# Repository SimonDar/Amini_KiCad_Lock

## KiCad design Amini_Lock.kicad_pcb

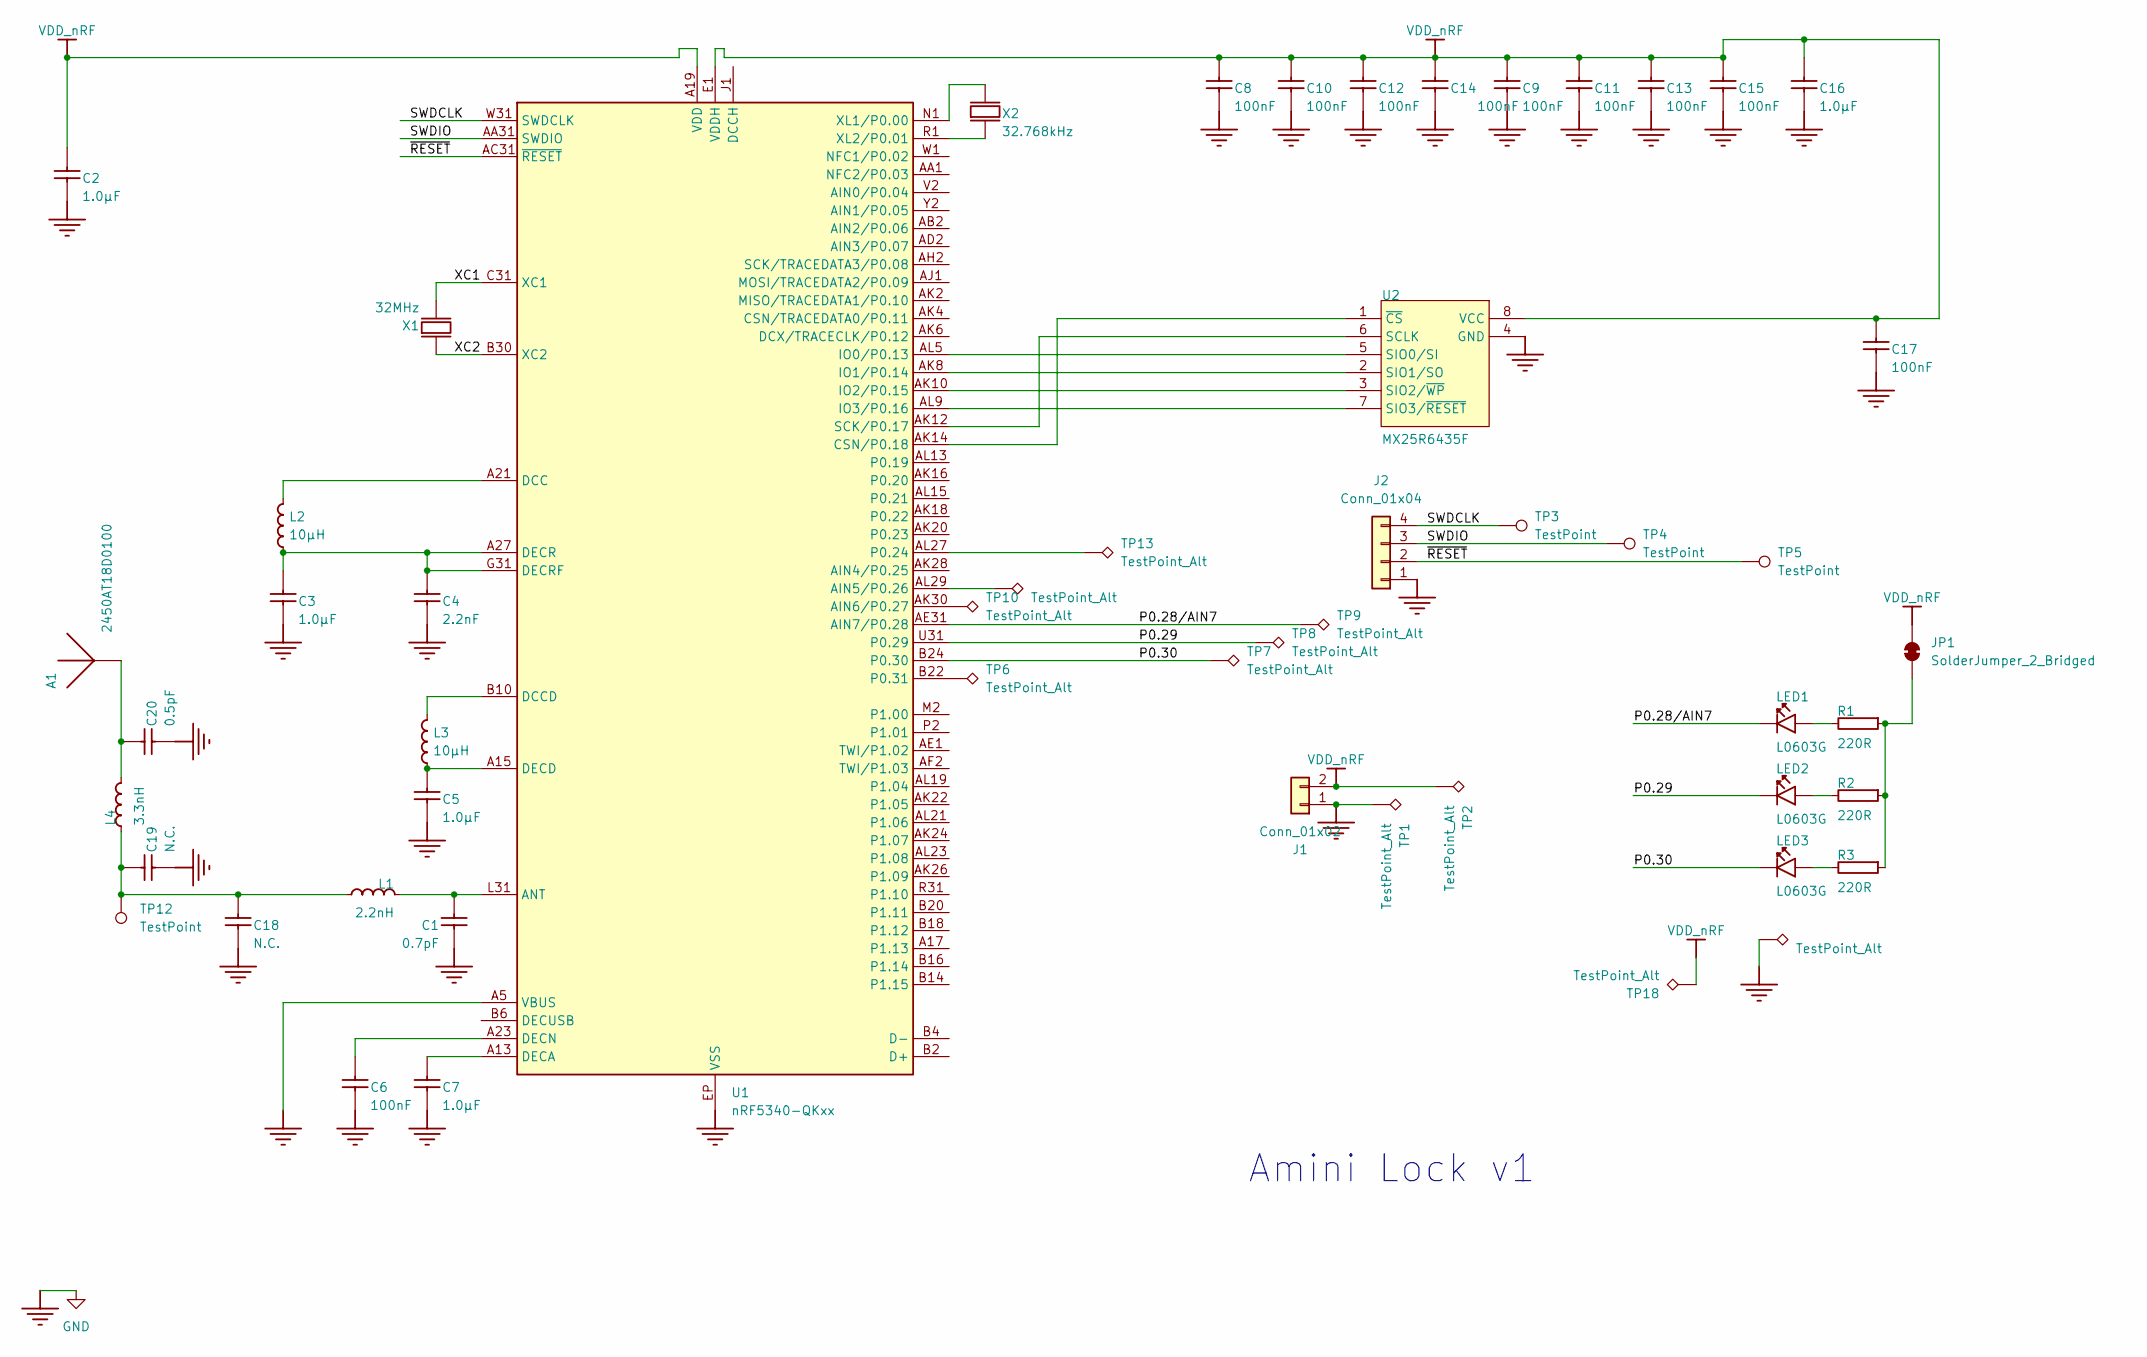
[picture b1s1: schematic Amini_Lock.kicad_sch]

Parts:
A1: 2450AT18D0100; 2450AT18D0100_STD-R; PART NUMBER Johanson 2450AT18D0100_STD-R
C1: 0.7pF; CAPC0603X03L_C; PART NUMBER C0201-0.7p-HQ-Murata
C2, C3, C5, C7, C16: 1.0µF; CAPC1005X04L
C4: 2.2nF; CAPC0603X03L_C
C6, C8, C9, C10, C11, C12, C13, C14, C15, C17: 100nF; CAPC0603X03L_C
C18: N.C.; CAPC0603X03L_C_NC; PART NUMBER C0201-N.C.
C19: N.C.; C_0201_0603Metric_Pad0.64x0.40mm_HandSolder; PART NUMBER C0201-N.C.
C20: 0.5pF; CAPC0603X03L_C; PART NUMBER C0201-0.5p
J1: Conn_01x02; JST_SH_BM02B-SRSS-TB_1x02-1MP_P1.00mm_Vertical
J2: Conn_01x04; JST_SH_SM04B-SRSS-TB_1x04-1MP_P1.00mm_Horizontal
JP1: SolderJumper_2_Bridged; SolderJumper-2_P1.3mm_Bridged_RoundedPad1.0x1.5mm_1
L1: 2.2nH; INDC0603X03L_C; PART NUMBER L0201-2n2-HQ-Murata
L2, L3: 10µH; INDC1608X06L
L4: 3.3nH; INDC0603X03L_C; PART NUMBER L0201-3n3-HQ-Murata
LED1, LED2, LED3: L0603G; LED_0603_1608Metric; PART NUMBER VS 25C7M5
R1, R2, R3: 220R; RESC0603X03L_C; PART NUMBER R0201-220
TP1, TP2: TestPoint_Alt; TestPoint_Pad_1.5x1.5mm
TP3, TP4, TP5: TestPoint; TestPoint_Pad_D1.0mm
TP6, TP7, TP8, TP9, TP10, TP11, TP13, TP16, TP18: TestPoint_Alt; TestPoint_THTPad_2.0x2.0mm_Drill1.0mm
TP12: TestPoint; TestPoint_Pad_1.0x1.0mm
U1: nRF5340-QKxx; Nordic_AQFN-94-1EP_7x7mm_P0.4mm
U2: MX25R6435F; SON127P600X80_HS-9N; PART NUMBER MX25R6435FZNIL0
X1: 32MHz; BT-XTAL_2016
X2: 32.768kHz; XTAL_2012

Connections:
/P0.28/AIN7: LED1.1 (C), TP9.1, U1.AE31 (AIN7/P0.28)
/P0.29: LED2.1 (C), TP8.1, U1.U31 (P0.29)
/P0.30: LED3.1 (C), TP7.1, U1.B24 (P0.30)
/SWDCLK: J2.4, TP3.1, U1.W31 (SWDCLK)
/SWDIO: J2.3, TP4.1, U1.AA31 (SWDIO)
/XC1: U1.C31 (XC1), X1.1 (inp)
/XC2: U1.B30 (XC2), X1.3 (out)
/~RESET: J2.2, TP5.1, U1.AC31 (~RESET)
GND: A1.2 (GND), C1.1, C2.2, C3.1, C4.2, C5.1, C6.2, C7.1, C8.2, C9.2, C10.2, C11.2, C12.2, C13.2, C14.2, C15.2, C16.1, C17.2, C18.1, C19.1, C20.1, J1.1, J2.1, TP1.1, TP16.1, U1.A5 (VBUS), U1.EP (VSS), U2.4 (GND)
unnamed: A1.1, C20.2, L4.1
unnamed: C18.2, C19.2, L1.2, L4.2, TP12.1
unnamed: JP1.1 (A), R1.2, R2.2, R3.2
unnamed: LED1.2 (A), R1.1
unnamed: LED2.2 (A), R2.1
unnamed: LED3.2 (A), R3.1
unnamed: TP11.1, U1.AL29 (AIN5/P0.26)
unnamed: TP10.1, U1.AK30 (AIN6/P0.27)
unnamed: C1.2, L1.1, U1.L31 (ANT)
unnamed: U1.AK14 (CSN/P0.18), U2.1 (~CS)
unnamed: L2.2, U1.A21 (DCC)
unnamed: L3.2, U1.B10 (DCCD)
unnamed: C7.2, U1.A13 (DECA)
unnamed: C5.2, L3.1, U1.A15 (DECD)
unnamed: C6.1, U1.A23 (DECN)
unnamed: C3.2, C4.1, L2.1, U1.A27 (DECR), U1.G31 (DECRF)
unnamed: U1.AL5 (IO0/P0.13), U2.5 (SIO0/SI)
unnamed: U1.AK8 (IO1/P0.14), U2.2 (SIO1/SO)
unnamed: U1.AK10 (IO2/P0.15), U2.3 (SIO2/~WP)
unnamed: U1.AL9 (IO3/P0.16), U2.7 (SIO3/~RESET)
unnamed: TP13.1, U1.AL27 (P0.24)
unnamed: TP6.1, U1.B22 (P0.31)
unnamed: U1.AK12 (SCK/P0.17), U2.6 (SCLK)
unnamed: U1.N1 (XL1/P0.00), X2.1 (inp)
unnamed: U1.R1 (XL2/P0.01), X2.2 (out)
VDD_nRF: C2.1, C8.1, C9.1, C10.1, C11.1, C12.1, C13.1, C14.1, C15.1, C16.2, C17.1, J1.2, JP1.2 (B), TP2.1, TP18.1, U1.A19 (VDD), U1.AC1 (VDD), U1.AG1 (VDD), U1.AJ31 (VDD), U1.AL3 (VDD), U1.AL7 (VDD), U1.AL11 (VDD), U1.AL17 (VDD), U1.AL25 (VDD), U1.B8 (VDD), U1.B28 (VDD), U1.C1 (VDD), U1.E1 (VDDH), U1.E31 (VDD), U1.L1 (VDD), U1.N31 (VDD), U1.U1 (VDD), U2.8 (VCC)

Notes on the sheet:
Amini Lock v1

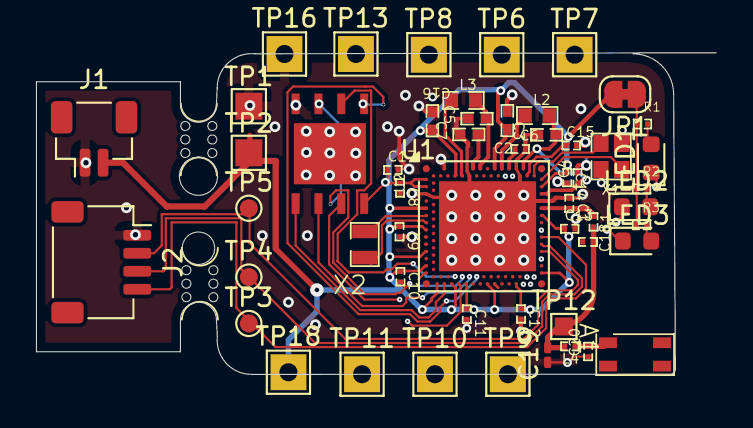
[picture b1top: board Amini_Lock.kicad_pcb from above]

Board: 4 copper layers, 37.8 x 17.9 mm, 55 parts (0 on the bottom side), 35 nets.

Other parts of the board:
mouse-bite-2mm-slot, mouse-bite-2mm-slot#2: VAL**; mouse-bite-2mm-slot

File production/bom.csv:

Designator,Footprint,Quantity,Value,LCSC Part #
"_6, _5, _4, _3, _2, ",7f799c2c-a0ec-4dfc-857c-f149acab8d33,6,,
A1,2450AT18D0100_STD-R,1,2450AT18D0100,
"C1, C18",0402,2,0,
"C10, C11, C12, C13, C14, C15, C6, C8, C9",CAPC0603X03L_C,9,100nF,
"C16, C2, C3, C5",CAPC1005X04L,4,1.0µF,
C17,0402,1,0.7pF,
C19,0402,1,N.C.,
C4,CAPC0603X03L_C,1,2.2nF,
C7,0402,1,1.0µF,
D1,0402,1,D,
J1,PinHeader_1x02_P2.00mm_Vertical,1,Conn_01x02_Pin,
J2,PinHeader_2x02_P2.54mm_Vertical,1,Conn_01x04,
J3,PinHeader_1x04_P2.00mm_Vertical,1,Conn_01x04_Pin,
L1,0402,1,0r,
"L2, L3",INDC1608X06L,2,10µH,
L4,0402,1,2.2nH,
"LED1, LED2, LED3",0603,3,L0603G,
"R1, R2, R3",RESC0603X03L_C,3,220R,
U1,Nordic_AQFN-94-1EP_7x7mm_P0.4mm,1,nRF5340-QKxx,
X1,BT-XTAL_2016,1,32MHz,
X2,XTAL_2012,1,32.768kHz,
"clk, gnd, io, set",TestPoint_Pad_D1.5mm,4,TestPoint,

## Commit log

2024-05-28 2. commit
2024-05-28 3. commit
2024-05-28 clear, every component on place, wrong with shematic
2024-05-28 clear, every component on place, component match kicad
2024-05-28 mousebites added
2024-05-29 backup before rework stackable boards
2024-05-30 backup mid routing
2024-05-30 backup almoast done routing - new space reorientation led
2024-05-30 Wireing done, no error
2024-05-31 Backup before trying to add secound filter surcit
2024-05-31 Backup of wrong way, went with two matching netwrk, konstanting gave me a heds up that i need only one and take ohm in wire into consideration
2024-05-31 New antenna design done
2024-06-02 some changes done
2024-06-20 backup
2024-06-20 fikset småting og endret logo
2024-06-20 fikset logo, ligger igjen søkkepø
2024-06-20 fikset logo, funker greit
2024-06-20 Trodde runde greier var hull, not hull
2024-06-20 klar for produksjon
2024-06-21 Produsert
2024-06-23 Added first revistion´
2024-06-25 Ryddet opp i schematics
2024-07-26 Removal of unnecesary items
2024-07-26 Adding V1.1
